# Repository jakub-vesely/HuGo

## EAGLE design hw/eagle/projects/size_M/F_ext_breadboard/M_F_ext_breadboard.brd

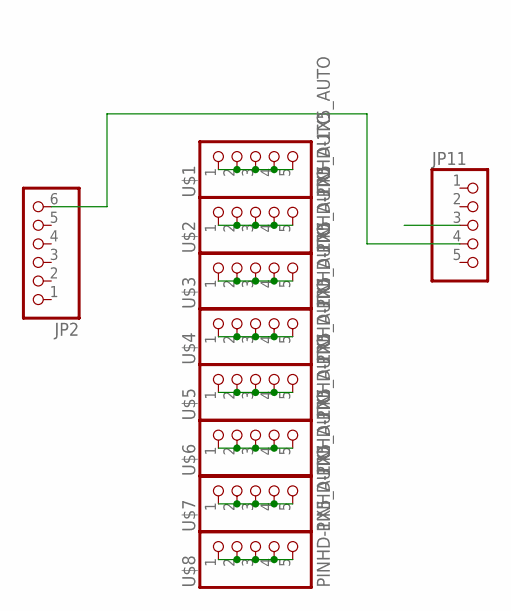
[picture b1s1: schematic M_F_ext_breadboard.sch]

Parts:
JP2: PINHD-1X6; 1X06
JP11: PINHD-1X5; 1X05
U$1, U$2, U$3, U$4, U$5, U$6, U$7, U$8: PINHD-1X5_AUTO; 1X5_AUTO

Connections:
GND: JP2.6, JP11.4
unnamed: U$1.1, U$1.2, U$1.3, U$1.4, U$1.5
unnamed: U$2.1, U$2.2, U$2.3, U$2.4, U$2.5
unnamed: U$3.1, U$3.2, U$3.3, U$3.4, U$3.5
unnamed: U$4.1, U$4.2, U$4.3, U$4.4, U$4.5
unnamed: U$5.1, U$5.2, U$5.3, U$5.4, U$5.5
unnamed: U$6.1, U$6.2, U$6.3, U$6.4, U$6.5
unnamed: U$7.1, U$7.2, U$7.3, U$7.4, U$7.5
unnamed: U$8.1, U$8.2, U$8.3, U$8.4, U$8.5
VDD: JP11.3

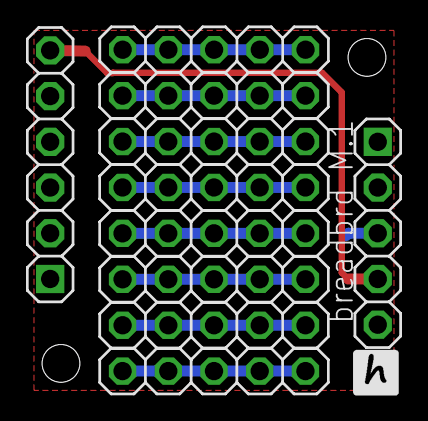
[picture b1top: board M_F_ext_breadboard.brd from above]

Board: 2 copper layers, 10 parts (0 on the bottom side), 9 nets.

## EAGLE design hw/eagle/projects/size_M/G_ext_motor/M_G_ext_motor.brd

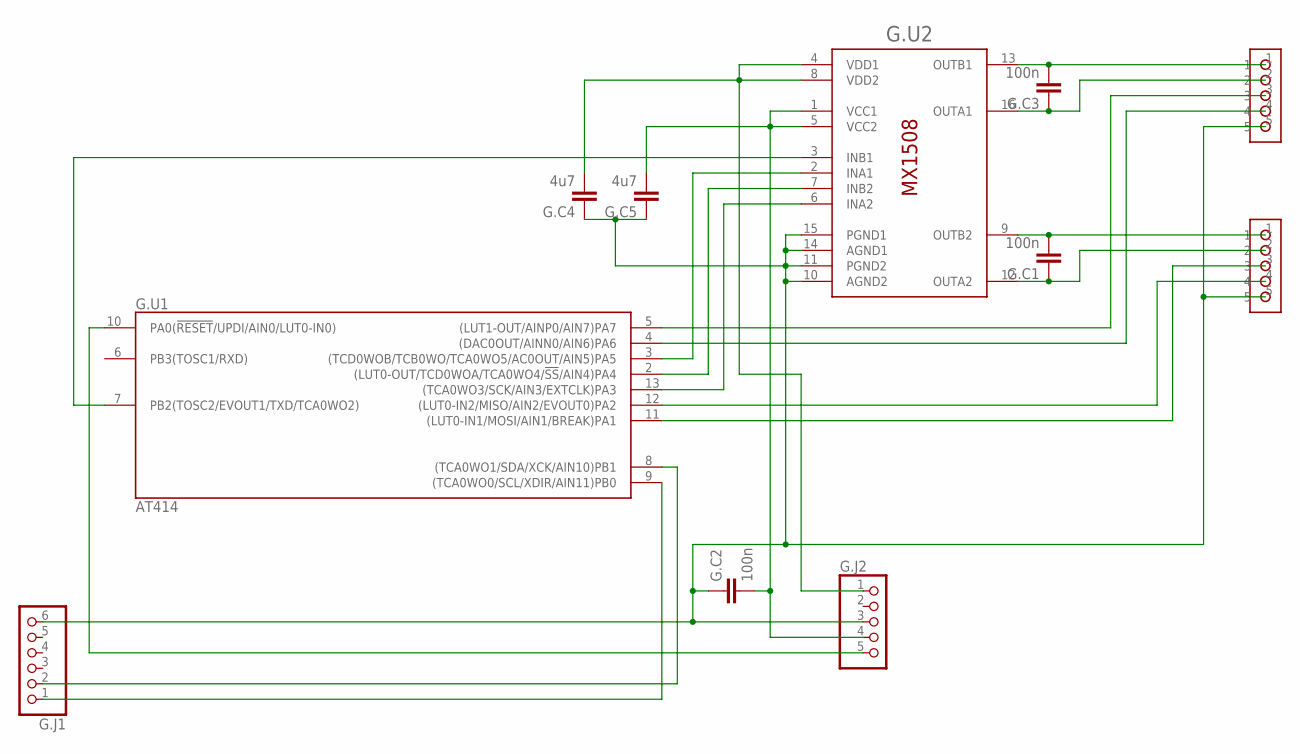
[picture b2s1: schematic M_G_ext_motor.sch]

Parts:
G.C1, G.C2, G.C3: 100n; C0603
G.C4, G.C5: 4u7; C0603
G.J1: PINHD-1X6; 1X06
G.J2: PINHD-1X5; 1X05
G.J3, G.MOTO1: A1250WR
G.U1: AT414; SO14
G.U2: MX1508; SOP16

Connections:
FOTO1: G.MOTO1.3, G.U1.5 ((LUT1-OUT/AINP0/AIN7)PA7)
FOTO2: G.J3.4, G.U1.12 ((LUT0-IN2/MISO/AIN2/EVOUT0)PA2)
GND: G.C2.1, G.C4.1, G.C5.1, G.J1.6, G.J2.3, G.J3.5, G.J3.$1 (GND), G.J3.$2 (GND), G.MOTO1.5, G.MOTO1.$1 (GND), G.MOTO1.$2 (GND), G.U1.14 (GND), G.U2.10 (AGND2), G.U2.11 (PGND2), G.U2.14 (AGND1), G.U2.15 (PGND1)
INA1: G.U1.3 ((TCD0WOB/TCB0WO/TCA0WO5/AC0OUT/AIN5)PA5), G.U2.2 (INA1)
INA2: G.U1.13 ((TCA0WO3/SCK/AIN3/EXTCLK)PA3), G.U2.6 (INA2)
INB1: G.U1.7 (PB2(TOSC2/EVOUT1/TXD/TCA0WO2)), G.U2.3 (INB1)
INB2: G.U1.2 ((LUT0-OUT/TCD0WOA/TCA0WO4/!SS!/AIN4)PA4), G.U2.7 (INB2)
LED1: G.MOTO1.4, G.U1.4 ((DAC0OUT/AINN0/AIN6)PA6)
LED2: G.J3.3, G.U1.11 ((LUT0-IN1/MOSI/AIN1/BREAK)PA1)
M1: G.C3.2, G.MOTO1.1, G.U2.13 (OUTB1)
M2: G.C3.1, G.MOTO1.2, G.U2.16 (OUTA1)
M3: G.C1.2, G.J3.1, G.U2.9 (OUTB2)
M4: G.C1.1, G.J3.2, G.U2.12 (OUTA2)
M_SRC: G.C4.2, G.J2.1, G.U2.4 (VDD1), G.U2.8 (VDD2)
unnamed: G.J2.5, G.U1.10 (PA0(!RESET!/UPDI/AIN0/LUT0-IN0))
unnamed: G.J1.1, G.U1.9 ((TCA0WO0/SCL/XDIR/AIN11)PB0)
unnamed: G.J1.2, G.U1.8 ((TCA0WO1/SDA/XCK/AIN10)PB1)
VCC: G.C2.2, G.C5.2, G.J2.4, G.U1.1 (VCC), G.U2.1 (VCC1), G.U2.5 (VCC2)

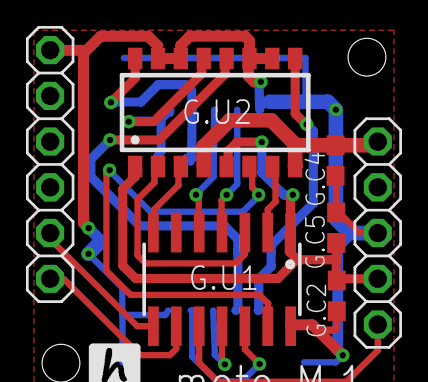
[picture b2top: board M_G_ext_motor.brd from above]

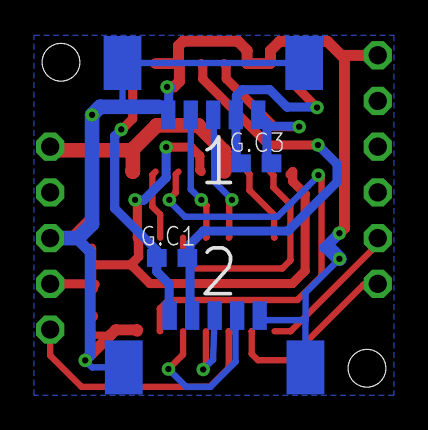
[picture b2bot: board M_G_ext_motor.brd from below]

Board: 2 copper layers, 11 parts (4 on the bottom side), 18 nets.

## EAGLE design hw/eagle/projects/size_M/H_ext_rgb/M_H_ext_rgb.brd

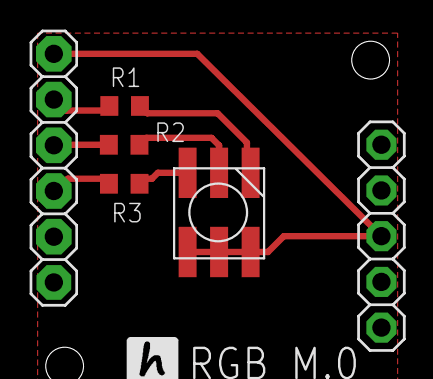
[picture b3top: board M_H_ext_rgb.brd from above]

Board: 2 copper layers, 6 parts (0 on the bottom side), 7 nets.

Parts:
JP2: 1X06
JP3: 1X05
R1, R2, R3: 330; R0603
U$2: RGB_WW-FCE50TC-Q1

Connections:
GND: JP2.6, JP3.3, U$2.4, U$2.5, U$2.6
unnamed: R1.2, U$2.1
unnamed: R3.2, U$2.3
unnamed: R2.2, U$2.2
unnamed: JP2.5, R1.1
unnamed: JP2.4, R2.1
unnamed: JP2.3, R3.1

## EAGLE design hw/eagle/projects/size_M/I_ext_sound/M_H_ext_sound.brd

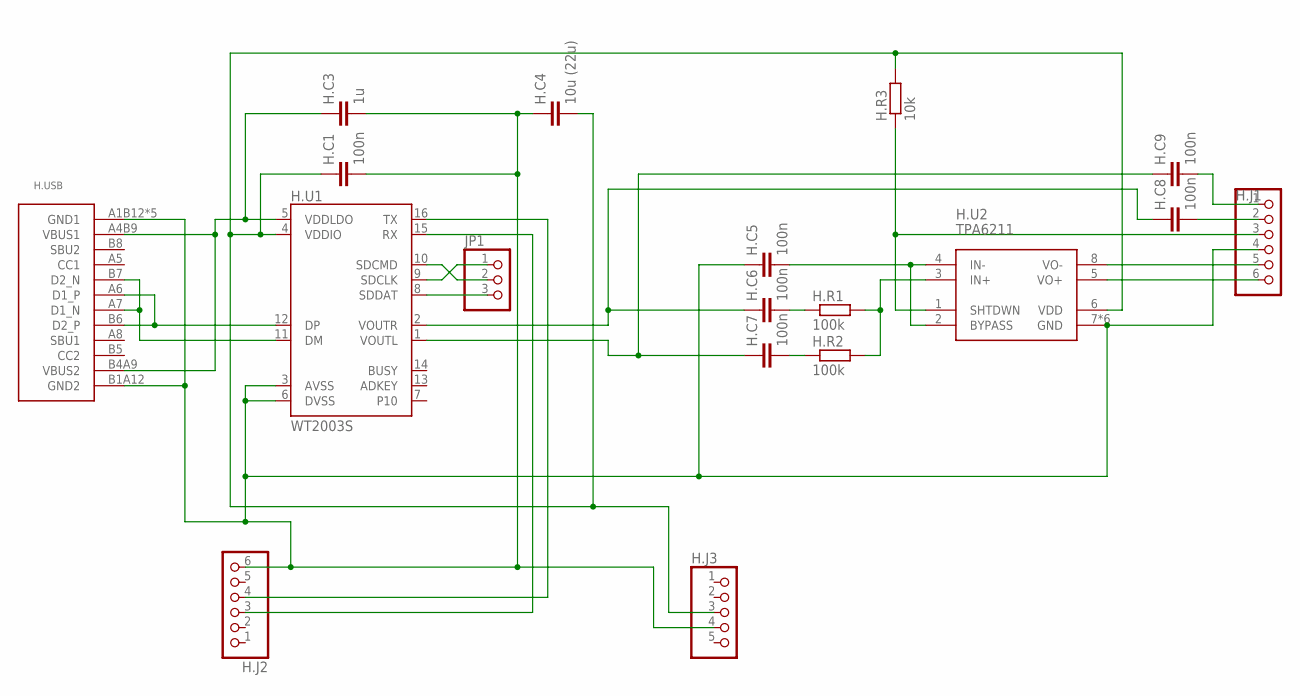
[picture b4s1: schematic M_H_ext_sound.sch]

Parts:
H.C1, H.C5, H.C6, H.C7, H.C8, H.C9: 100n; C0603
H.C3: 1u; C0603
H.C4: 10u (22u); C0805
H.J1, H.J2: PINHD-1X6; 1X06
H.J3: PINHD-1X5; 1X05
H.R1, H.R2: 100k; R0603
H.R3: 10k; R0603
H.U1: WT2003S; SO16
H.U2: TPA6211; MSOP-POWERPAD-8
H.USB: USB-C
JP1: PINHD-1X3; 1X03

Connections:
GND: H.C1.2, H.C3.2, H.C4.1, H.C5.1, H.J1.4, H.J2.6, H.J3.4, H.U1.3 (AVSS), H.U1.6 (DVSS), H.U2.7 (GND), H.U2.9 (GND), H.U2.P$10 (GND), H.U2.P$11 (GND), H.U2.P$12 (GND), H.U2.P$13 (GND), H.USB.A1B12 (GND1), H.USB.B1A12 (GND2), H.USB.SH1 (GND1), H.USB.SH2 (GND1), H.USB.SH3 (GND1), H.USB.SH4 (GND1)
unnamed: H.C8.2, H.J1.2
unnamed: H.C9.2, H.J1.1
unnamed: H.J1.5, H.U2.8 (VO-)
unnamed: H.J2.3, H.U1.15 (RX)
unnamed: H.J2.4, H.U1.16 (TX)
unnamed: H.J1.6, H.U2.5 (VO+)
unnamed: H.J1.3, H.R3.1, H.U2.1 (SHTDWN)
unnamed: H.U1.10 (SDCMD), JP1.2
unnamed: H.U1.12 (DP), H.USB.A6 (D1_P), H.USB.B6 (D2_P)
unnamed: H.U1.11 (DM), H.USB.A7 (D1_N), H.USB.B7 (D2_N)
unnamed: H.C3.1, H.U1.5 (VDDLDO), H.USB.A4B9 (VBUS1), H.USB.B4A9 (VBUS2)
unnamed: H.C6.1, H.C8.1, H.U1.2 (VOUTR)
unnamed: H.C7.1, H.C9.1, H.U1.1 (VOUTL)
unnamed: H.R1.2, H.R2.2, H.U2.3 (IN+)
unnamed: H.C5.2, H.U2.2 (BYPASS), H.U2.4 (IN-)
unnamed: H.U1.9 (SDCLK), JP1.1
unnamed: H.C6.2, H.R1.1
unnamed: H.C7.2, H.R2.1
unnamed: H.U1.8 (SDDAT), JP1.3
VCC: H.C1.1, H.C4.2, H.J3.3, H.R3.2, H.U1.4 (VDDIO), H.U2.6 (VDD)

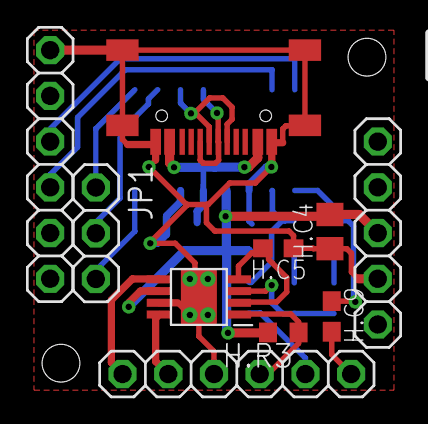
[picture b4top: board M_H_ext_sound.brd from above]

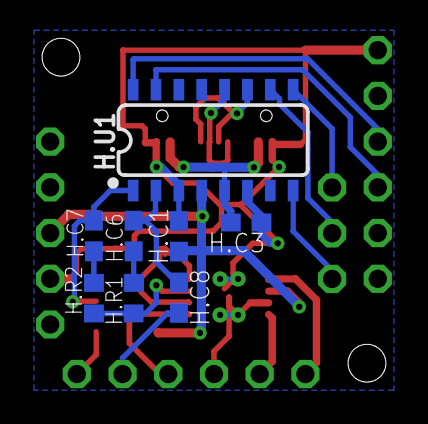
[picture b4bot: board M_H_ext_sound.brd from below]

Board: 2 copper layers, 18 parts (8 on the bottom side), 21 nets.

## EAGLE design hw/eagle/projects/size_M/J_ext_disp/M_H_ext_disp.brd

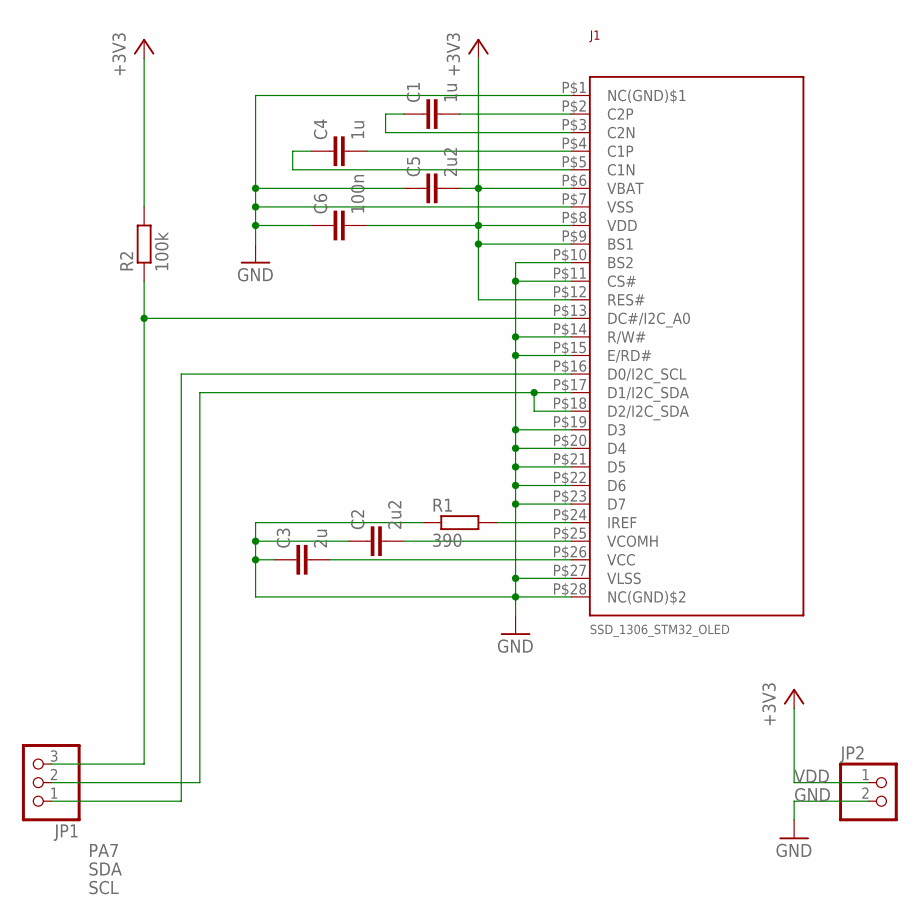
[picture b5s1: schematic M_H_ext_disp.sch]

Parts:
C1, C4: 1u; C0603
C2, C5: 2u2; C0603
C3: 2u; C0603
C6: 100n; C0603
J1: SSD_1306_STM32_OLED
JP1: PINHD-1X3; 1X03
JP2: PINHD-1X2; 1X02
R1: 390; R0603
R2: 100k; R0603

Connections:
GND: C2.1, C3.1, C5.1, C6.1, J1.P$1 (NC(GND)$1), J1.P$7 (VSS), J1.P$10 (BS2), J1.P$11 (CS#), J1.P$14 (R/W#), J1.P$15 (E/RD#), J1.P$19 (D3), J1.P$20 (D4), J1.P$21 (D5), J1.P$22 (D6), J1.P$23 (D7), J1.P$27 (VLSS), J1.P$28 (NC(GND)$2), JP2.2, R1.1
unnamed: J1.P$24 (IREF), R1.2
unnamed: C3.2, J1.P$26 (VCC)
unnamed: C2.2, J1.P$25 (VCOMH)
unnamed: C1.2, J1.P$2 (C2P)
unnamed: C1.1, J1.P$3 (C2N)
unnamed: C4.2, J1.P$4 (C1P)
unnamed: C4.1, J1.P$5 (C1N)
PA7: J1.P$13 (DC#/I2C_A0), JP1.3, R2.1
SCL: J1.P$16 (D0/I2C_SCL), JP1.1
SDA: J1.P$17 (D1/I2C_SDA), J1.P$18 (D2/I2C_SDA), JP1.2
VDD: C5.2, C6.2, J1.P$6 (VBAT), J1.P$8 (VDD), J1.P$9 (BS1), J1.P$12 (RES#), JP2.1, R2.2

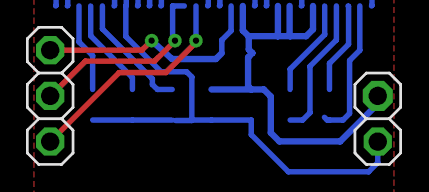
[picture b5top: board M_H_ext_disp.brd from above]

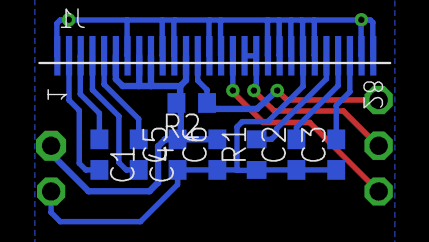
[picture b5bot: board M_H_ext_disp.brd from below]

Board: 2 copper layers, 11 parts (8 on the bottom side), 12 nets.

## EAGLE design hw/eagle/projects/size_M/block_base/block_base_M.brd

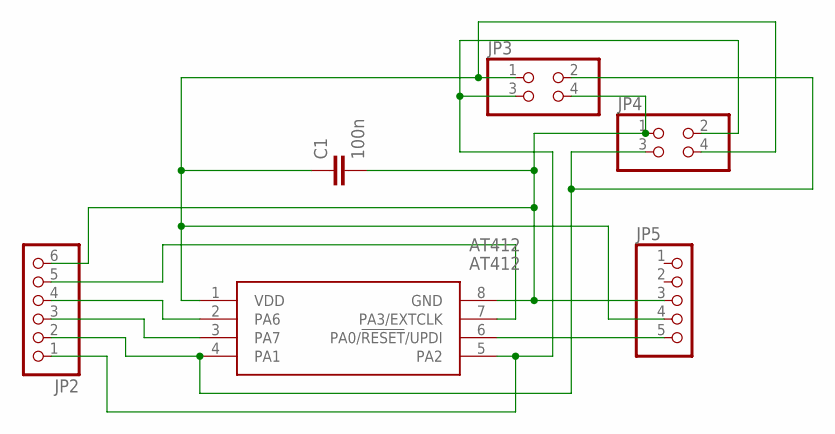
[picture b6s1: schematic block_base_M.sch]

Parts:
AT412: AT412; SOIC127P600X175-8N
C1: 100n; C0805K
JP2: PINHD-1X6; 1X06
JP3, JP4: PINHD-2X2; 2X02
JP5: PINHD-1X5; 1X05

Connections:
GND: AT412.8 (GND), C1.2, JP2.6, JP3.4, JP4.1, JP5.3
PA3: AT412.7 (PA3/EXTCLK), JP2.5
PA6: AT412.2 (PA6), JP2.4
PA7: AT412.3 (PA7), JP2.3
SCL: AT412.5 (PA2), JP2.1, JP3.3, JP4.2
SDA: AT412.4 (PA1), JP2.2, JP3.2, JP4.3
UPDI: AT412.6 (PA0/!RESET!/UPDI), JP5.5
VDD: AT412.1 (VDD), C1.1, JP3.1, JP4.4, JP5.4

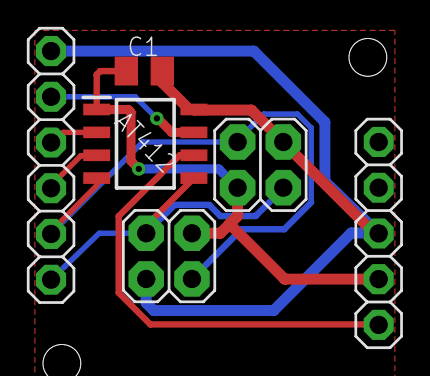
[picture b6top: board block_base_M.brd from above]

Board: 2 copper layers, 6 parts (0 on the bottom side), 8 nets.

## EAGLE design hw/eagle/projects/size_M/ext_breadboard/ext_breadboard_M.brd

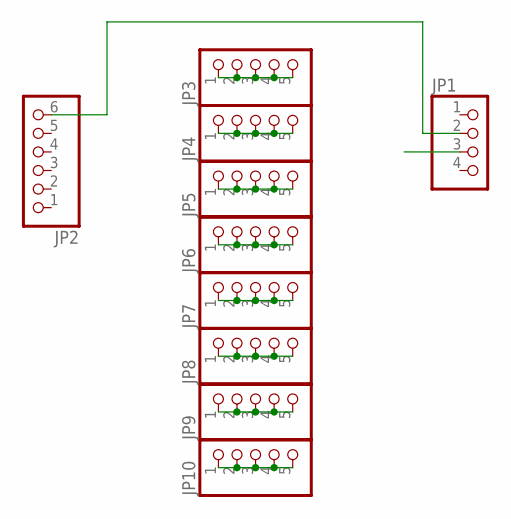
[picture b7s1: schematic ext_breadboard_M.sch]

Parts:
JP1: PINHD-1X4; 1X04
JP2: PINHD-1X6; 1X06
JP3, JP4, JP5, JP6, JP7, JP8, JP9, JP10: PINHD-1X5; 1X05

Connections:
GND: JP1.2, JP2.6
unnamed: JP3.1, JP3.2, JP3.3, JP3.4, JP3.5
unnamed: JP4.1, JP4.2, JP4.3, JP4.4, JP4.5
unnamed: JP5.1, JP5.2, JP5.3, JP5.4, JP5.5
unnamed: JP6.1, JP6.2, JP6.3, JP6.4, JP6.5
unnamed: JP7.1, JP7.2, JP7.3, JP7.4, JP7.5
unnamed: JP8.1, JP8.2, JP8.3, JP8.4, JP8.5
unnamed: JP9.1, JP9.2, JP9.3, JP9.4, JP9.5
unnamed: JP10.1, JP10.2, JP10.3, JP10.4, JP10.5
VDD: JP1.3

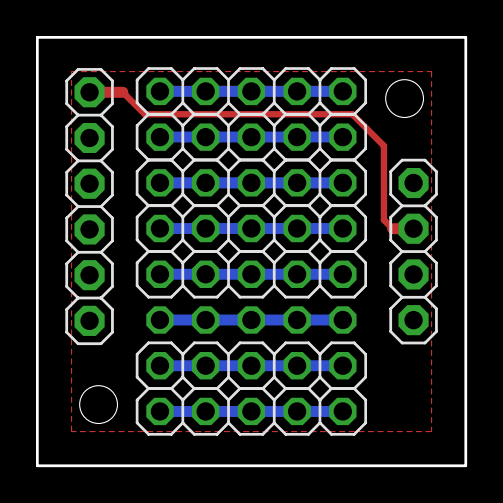
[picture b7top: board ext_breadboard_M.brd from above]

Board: 2 copper layers, 23.8 x 23.8 mm, 10 parts (1 on the bottom side), 9 nets.

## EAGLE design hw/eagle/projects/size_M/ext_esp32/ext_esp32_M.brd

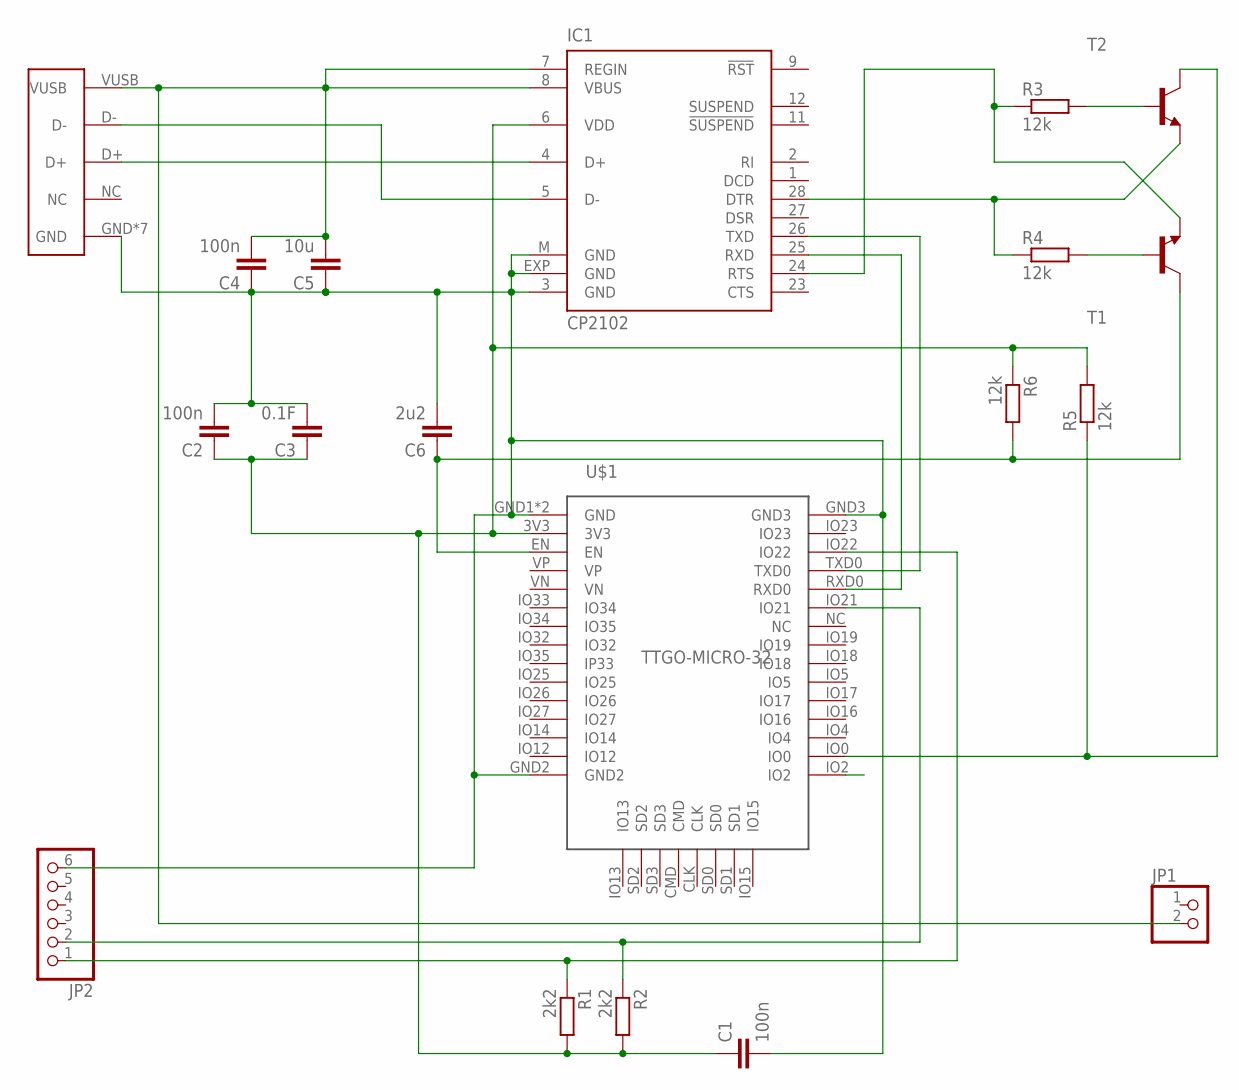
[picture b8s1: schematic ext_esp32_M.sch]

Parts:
C1, C2, C4: 100n; C0603
C3: 0.1F; C0603
C5: 10u; C0603
C6: 2u2; C0603
IC1: CP2102; MLP28
JP1: PINHD-1X2; 1X02
JP2: PINHD-1X6; 1X06
R1, R2: 2k2; R0603
R3, R4, R5, R6: 12k; R0603
T1, T2: BC808-NPN-SOT23-BEC; SOT23-BEC
U$1: TTGO-MICRO-32
USB: MICRO-USB

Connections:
DTR: IC1.28 (DTR), R4.1, T2.E
GND: C1.2, C2.2, C3.2, C4.1, C5.1, C6.2, IC1.3 (GND), IC1.EXP (GND), IC1.M (GND), JP2.6, U$1.GND1 (GND), U$1.GND2, U$1.GND3, U$1.GND4 (GND), USB.GND, USB.GND1 (GND), USB.GND2 (GND), USB.GND3 (GND), USB.GND4 (GND), USB.P$1 (GND), USB.P$2 (GND)
unnamed: IC1.5 (D-), USB.D-
unnamed: IC1.4 (D+), USB.D+
unnamed: IC1.26 (TXD), U$1.TXD0
unnamed: R4.2, T1.B
unnamed: IC1.25 (RXD), U$1.RXD0
unnamed: R3.2, T2.B
unnamed: R5.1, T2.C, U$1.IO0
unnamed: C6.1, R6.2, T1.C, U$1.EN
RTS: IC1.24 (RTS), R3.1, T1.E
SCL: JP2.1, R1.1, U$1.IO22
SDA: JP2.2, R2.1, U$1.IO21
VDD: C1.1, C2.1, C3.1, IC1.6 (VDD), R1.2, R2.2, R5.2, R6.1, U$1.3V3
VUSB: C4.2, C5.2, IC1.7 (REGIN), IC1.8 (VBUS), JP1.2, USB.VUSB

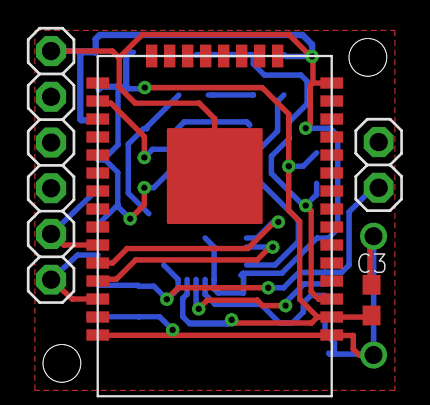
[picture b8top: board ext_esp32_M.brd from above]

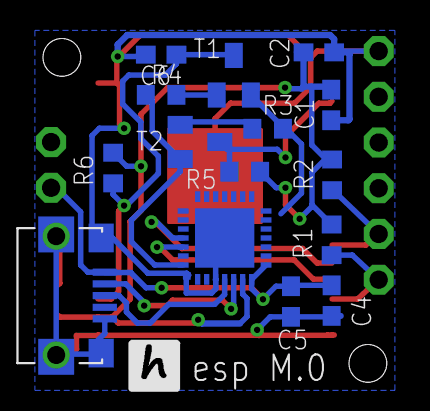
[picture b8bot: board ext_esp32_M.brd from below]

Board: 2 copper layers, 19 parts (15 on the bottom side), 15 nets.
